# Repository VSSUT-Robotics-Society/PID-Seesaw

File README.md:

# PID Seesaw

## Overview

The PID Seesaw project demonstrates the application of a Proportional-Integral-Derivative (PID) controller to balance a seesaw (inverted pendulum) system. The objective is to maintain the ball's position by dynamically adjusting the control input based on real-time feedback from the system.

<div align="center">

</div>

## System Description

- **Plant:** The system consists of a seesaw with a ball mounted on a pivot, which is inherently unstable and requires active control to maintain balance.
- **Sensor:** A distance sensor is used to measure the distance of the ball from an extreme end of the seesaw.
- **Actuator:** A servo applies corrective torque or force to bring the ball back to the set point.
- **Controller:** The PID controller processes the error signal (difference between the desired and actual position) and computes the control action.

## PID Control Algorithm

The PID controller output is given by:

```
u(t) = Kp * e(t) + Ki * ∫e(t)dt + Kd * de(t)/dt
```

Where:
- `e(t)`: Error signal (desired position - measured position)
- `Kp`: Proportional gain (reacts to current error)
- `Ki`: Integral gain (reacts to accumulated error)
- `Kd`: Derivative gain (reacts to rate of error change)

Tuning these gains is essential for achieving a balance between responsiveness and stability.

## Implementation Steps

1. **System Modeling:** Derive and linearize the equations of motion for the seesaw.
2. **Sensor Integration:** Connect and calibrate the distance sensor for accurate feedback.
3. **Controller Design:** Implement the PID algorithm in software (e.g., Arduino, MATLAB, or Python).
4. **Tuning:** Adjust `Kp`, `Ki`, and `Kd` to minimize overshoot, settling time, and steady-state error.
5. **Testing:** Apply disturbances and observe the system's ability to return to equilibrium.
6. **Analysis:** Record and analyze the system's response to various test cases.

## Results and Discussion

- The PID controller can effectively stabilize the seesaw when properly tuned.
- The proportional term provides immediate correction, the integral term eliminates steady-state error, and the derivative term helps dampen oscillations.
- Challenges include sensor noise, actuator limitations, and non-linearities in the physical system.
- Experimental results show that the system can reject small disturbances and maintain balance, with performance depending on the quality of tuning and hardware.

## Applications

- Robotics and automation
- Educational demonstrations of feedback control
- Research in control systems and mechatronics

## References

[PID Seesaw - Report](PID%20Seesaw%20-%20Report.pdf) - A detailed report on the PID Seesaw project, including mathematical modeling, implementation details, and experimental results.

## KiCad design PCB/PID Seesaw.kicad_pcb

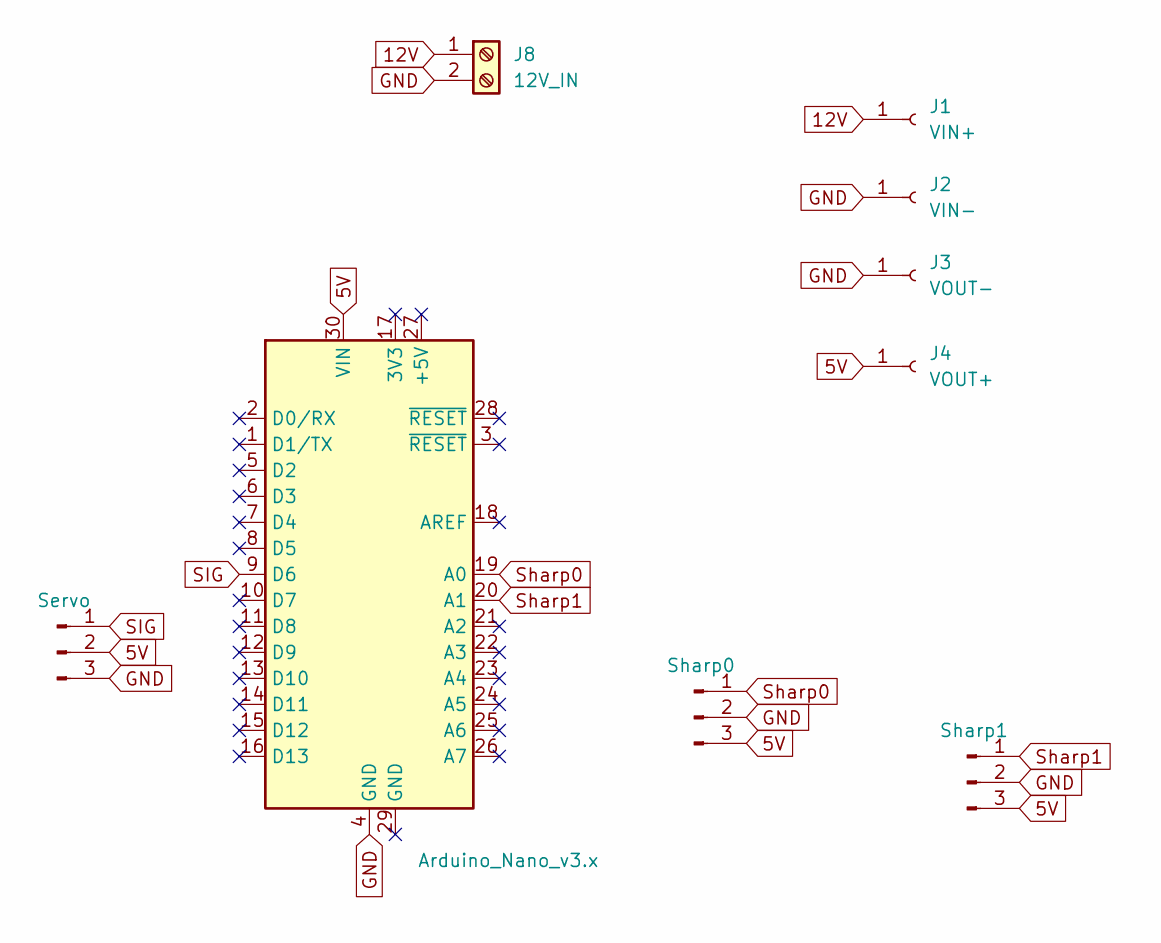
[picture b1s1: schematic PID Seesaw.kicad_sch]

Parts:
A1: Arduino_Nano_v3.x; Arduino_Nano
J1: VIN+; PinHeader_1x01_P2.54mm_Vertical
J2: VIN-; PinHeader_1x01_P2.54mm_Vertical
J3: VOUT-; PinHeader_1x01_P2.54mm_Vertical
J4: VOUT+; PinHeader_1x01_P2.54mm_Vertical
J5: Sharp0; PinHeader_1x03_P2.54mm_Vertical
J6: Sharp1; PinHeader_1x03_P2.54mm_Vertical
J7: Servo; PinHeader_1x03_P2.54mm_Vertical
J8: 12V_IN; TerminalBlock_bornier-2_P5.08mm

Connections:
5V: A1.30 (VIN), J4.1, J5.3, J6.3, J7.2
12V: J1.1, J8.1
GND: A1.4 (GND), J2.1, J3.1, J5.2, J6.2, J7.3, J8.2
SIG: A1.9 (D6), J7.1
Sharp0: A1.19 (A0), J5.1
Sharp1: A1.20 (A1), J6.1

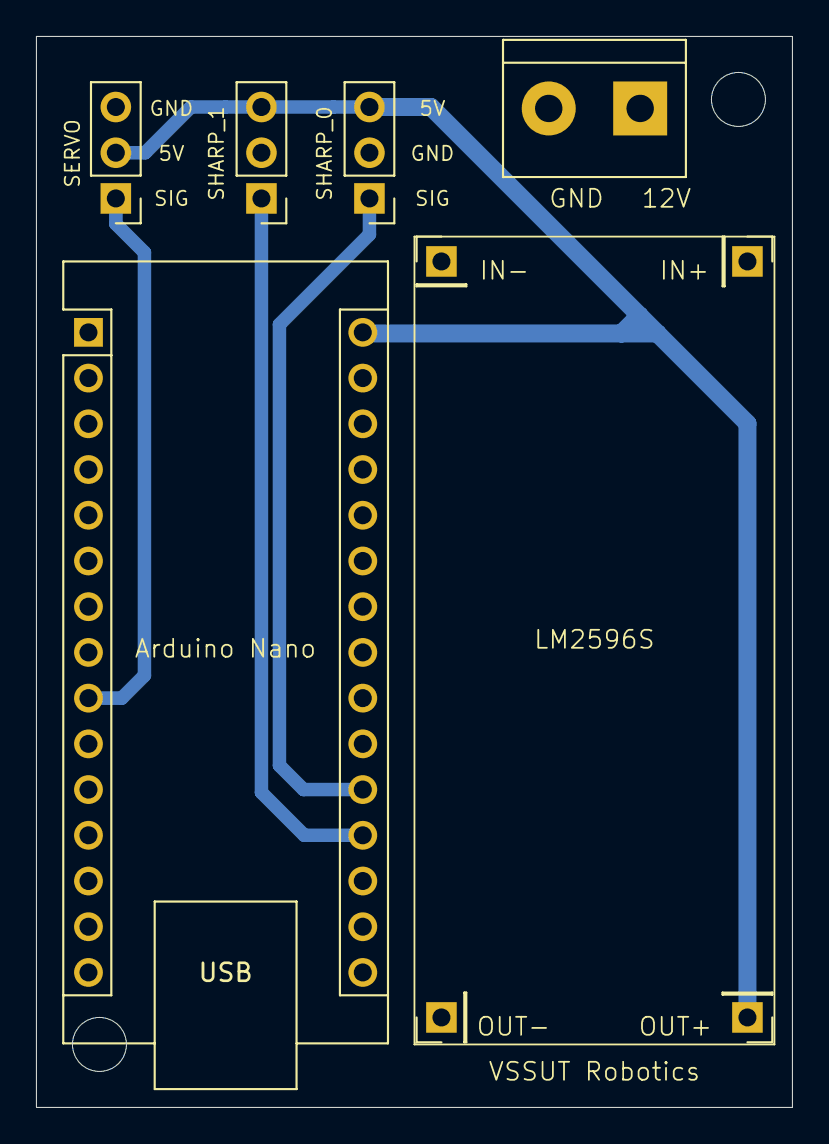
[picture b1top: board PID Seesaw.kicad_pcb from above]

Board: 2 copper layers, 42.0 x 59.5 mm, 9 parts (0 on the bottom side), 6 nets.

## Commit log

2025-06-17 Added assets & docs, Updated README.md
2025-06-18 First code to Understand PID and how it works step-by-step
2025-06-18 First attempt at a semi-working Seesaw
2025-06-18 First working Seesaw code; albeit not tuned properly
2025-07-04 First PCB design implementation
2025-09-04 Create PidSeeSaw.ino
    Code for pid see saw
